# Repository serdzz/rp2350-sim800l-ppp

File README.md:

# RP2350-Plus + SIM800L → PPP → embassy-net

Embassy-приложение для Waveshare RP2350-Plus, которое поднимает интернет через
GSM-модуль SIM800L: настройка модема на `atat`, IP-канал на `embassy-net-ppp`,
сокеты на `embassy-net`.

```
┌──────────── командный режим ────────────┐   ┌──────── data-режим ────────┐
 BufferedUart ──► atat::Ingress ──► ResponseSlot / UrcChannel
      ▲                                          BufferedUart ──► embassy-net-ppp
      └── atat::Client ── AT+CGDCONT / ATD*99#                          │
                                                          embassy-net (TCP/UDP/DNS)
```

Один и тот же UART обслуживает обе фазы, но **никогда одновременно**. Пока идёт
AT-настройка, задача ingress живёт внутри `select` и снимается автоматически, как
только модем ответил `CONNECT`. После этого UART целиком уходит в
`embassy_net_ppp::Runner::run`. Когда PPP-сессия разваливается, приложение шлёт
`+++` / `ATH`, возвращается в командный режим и повторяет цикл.

## Документация

* [ARCHITECTURE.md](ARCHITECTURE.md) — как собрана прошивка: задачи, потоки
  данных, ключевые решения и расход ресурсов.
* [hardware/nri-g13-shifter/](hardware/nri-g13-shifter/) — схема переходника
  монетоприёмника на BSS138 (KiCad).
* [docs/cmux.md](docs/cmux.md) — мультиплексор 27.010: формат кадров, ловушки
  спецификации, раздача каналов и находки на живом железе.

## Файлы

| Файл | Что внутри |
|---|---|
| `src/main.rs` | Инициализация периферии, стек, главный цикл «AT → PPP → восстановление» |
| `src/config.rs` | **APN, логин/пароль, строка дозвона, таймауты** — правьте здесь |
| `src/modem.rs` | AT-команды, ответы и URC для `atat` |
| `src/sim800l.rs` | Питание модуля и последовательность инициализации до `CONNECT` |
| `src/cmux.rs` | Протокол 27.010: кадры, сессия, управляющий канал — см. [docs/cmux.md](docs/cmux.md) |
| `src/cmux_transport.rs` | Раздача каналов CMUX поверх одного UART |
| `src/mqtt.rs` | Телеметрия и приём SMS в MQTT, подписка на команды |
| `src/led.rs` | Режимы зелёного светодиода на GP25 |
| `src/display.rs` | Экран SSD1306 по I2C: часы, заряд, шкала сигнала, состояние связи |
| `src/fuel.rs` | Топливомер MAX17048 на той же шине I2C |
| `src/coin.rs` | Кредит, коды монет, разбор команд (без зависимостей, тесты на хосте) |
| `src/coin_io.rs` | Линии монетоприёмника NRI G-13: снятие кода монеты и блокировка |
| `src/clock.rs` | Время от сети и шкала сигнала (без зависимостей, тесты на хосте) |
| `src/health.rs` | Счётчики обрывов связи (без зависимостей, тесты на хосте) |
| `src/app.rs` | Демо-нагрузка поверх поднятого IP: DNS + HTTP GET |
| `src/battery.rs` | Замер VSYS/VBAT, определение источника питания |
| `src/lipo.rs` | Кривая заряда Li-Po (без зависимостей, тестируется на хосте) |
| `src/fmt.rs` | Фасад логирования: `info!`/`warn!`/`unwrap!` → defmt или log |
| `src/usb_logger.rs` | USB CDC-ACM логгер (только в сборке `log-usb`) |
| `src/io_compat.rs` | Мост `embedded-io-async` 0.7 ↔ 0.6 (см. «Версии крейтов») |
| `at-tests/` | Хостовые тесты формата AT-команд и дайджестера |

## Схема подключения

| SIM800L | RP2350-Plus | Примечание |
|---|---|---|
| `TXD` | `GP1` (UART0 RX) | |
| `RXD` | `GP0` (UART0 TX) | **нужен делитель 3.3 В → 2.8 В** |
| `PWRKEY` | `GP2` | опционально, если модуль не стартует сам |
| — | `GP16` / `GP17` | SDA / SCL: экран SSD1306 и топливомер MAX17048 (I2C0) |
| — | `GP3`…`GP8` | линии монетоприёмника, см. ниже |
| `GND` | `GND` | общая земля обязательна |
| `VCC` | **отдельный источник 3.4–4.4 В** | 2 А импульсами |

Два момента, на которых спотыкается большинство сборок:

1. **Питание.** SIM800L в момент передачи потребляет до 2 А. От пина `3V3` платы
   он не заработает — нужен отдельный источник (Li-Ion, LDO на 4 В) и
   конденсатор 1000 мкФ рядом с модулем. Симптом нехватки тока — URC
   `NORMAL POWER DOWN` в логе.
2. **Уровни.** Вход `RXD` модуля рассчитан на 2.8 В. Подавать на него 3.3 В
   напрямую — за пределами спецификации; поставьте делитель или преобразователь
   уровней. Выход `TXD` (2.8 В) RP2350 читает как логическую единицу без
   доработок.

Пины UART меняются в `src/main.rs` (`p.PIN_0` / `p.PIN_1`), но оставайтесь в
пределах одного `UART0` — иначе поправьте и `bind_interrupts!`.

## Топливомер MAX17048

SparkFun Qwiic Fuel Gauge вешается на ту же шину I2C, что и экран: `GP16` (SDA)
и `GP17` (SCL), адрес `0x36`. Аккумулятор подключается к самому топливомеру, а
не к плате — он меряет напряжение прямо на банке.

Заряд выводится на экран рядом с часами. Если топливомера нет, там стоит
прочерк: пустое место читалось бы как «показа заряда не предусмотрено».

### Зачем он, если есть замер VSYS

Затем, что `battery.rs` меряет не банку, а VSYS, и **при воткнутом USB о
батарее не говорит ничего** — VBUS через диод задаёт VSYS независимо от её
состояния. В логе это видно как «батарея не измеряется» в каждой строке.

У MAX17048 такого ограничения нет. И считает он заряд не по напряжению, а по
своей модели разряда: под нагрузкой напряжение проседает, и пересчёт
«вольты → проценты» врёт тем сильнее, чем больше ток. У модема этот ток
доходит до двух ампер.

### Про общую шину

Экран работает с шиной асинхронно, а крейт `max170xx` блокирующий. Свести их
удалось потому, что `embassy_rp::I2c` реализует оба трейта сразу: экран ходит
через асинхронную обёртку `I2cDevice`, а топливомер берёт мьютекс и обращается
к шине напрямую. Транзакция там короткая, пара байт, так что блокировка внутри
асинхронной задачи безобидна.

## Монетоприёмник NRI G-13

Вариант с шестью параллельными линиями (не последовательный интерфейс).

| Контакт разъёма | Сигнал | RP2350-Plus |
|---|---|---|
| 1 | `GND` | `GND` |
| 2 | `UB` +12 В | отдельный источник 10–16 В, ~20 мА |
| 7 | output line 1 | `GP3` |
| 8 | output line 2 | `GP4` |
| 9 | output line 3 | `GP5` |
| 10 | output line 4 | `GP6` |
| 3 | output line 5 | `GP7` |
| 4 | output line 6 | `GP8` |
| 6 | total blocking | `GP9` через ключ, см. ниже |

Нумерация контактов и линий не совпадает — сверяйтесь с таблицей, а не со
здравым смыслом.

Каждая линия **двунаправленная**: приёмник выдаёт по ней импульс 100 мс при
опознанной монете, и она же, удерживаемая в нуле, блокирует свой канал.
Поэтому в прошивке это `Flex`, а не обычный вход: открытый канал — вход с
подтяжкой, закрытый — выход, притянутый к земле. Высокий уровень на линию не
выдаётся никогда — с той стороны открытый коллектор.

### Согласование уровней: BSS138 на каждую линию

Линии приёмника живут в 12-вольтовом мире, плата — в 3,3-вольтовом, и по
каждой линии нужно и читать, и писать. Проверенное решение — **двунаправленный
преобразователь на BSS138**, по одному на линию:

```text
        +3.3 В (затвор)
             │
   GP3 ──────┤ BSS138 ├────── output line 1
   (вход с      (сток к приёмнику,
    подтяжкой)   исток к плате)
```

Внешние резисторы не нужны: со стороны платы работает встроенная подтяжка
RP2350 (её включает `Flex::set_pull(Pull::Up)`), со стороны приёмника — его
собственная. Так собран рабочий автомат на MSP430
(`bahilizator_svn/hardware/main_baord/coin.sch`, `Q10…Q15`), и там же прошивка
включает внутренние подтяжки контроллера.

Для справки, требования из схемы подключения (`G-13.6000-1 d`, стр. 22):

| | напряжение |
|---|---|
| блокировка канала | `≤ 1 В` |
| приём канала | `≥ 3,5 В` |
| допустимое на линии | до 35 В, до 150 мА |

Заводить линии на выводы напрямую **нельзя**: 3,3 В ниже порога приёма, и это
ещё до вопроса о том, что на линии может оказаться.

### Полная блокировка (контакт 6)

Закрывает приём целиком, независимо от поканальной маски. Активен **высоким**:
блокировка `≥ 3,5 В`, приём `≤ 1 В`, выдерживает до 35 В.

Схема та же, что у линий, плюс подтяжка стока к `+5 В` — так это сделано в
рабочем автомате (`Q5` и `R45` 10 кОм на той же схеме):

```text
                        +3.3 В        +5 В
                           │            │
                           │           10к
                           │            │
  GP9 ──10к── +3.3 В   ────┤ BSS138 ├───┴──── контакт 6 (total blocking)
```

Каскад **не инвертирует**: `GP9` высокий → полевик закрыт → 10к тянет линию к
5 В → блокировка. Поэтому в `src/config.rs`:

```rust
pub const COIN_TOTAL_BLOCK_INVERTED: bool = false;
```

Резистор 10 кОм от `GP9` к `+3.3 В` — не из схемы-образца, а добавка: без него
вывод в сбросе не управляется, линия уходит к нулю, и **мёртвый автомат
принимает монеты, не давая кредита**. С подтяжкой неуправляемый вывод означает
«заблокировано».

Если собрали инвертирующий каскад (например, NPN с подтяжкой к +12 В),
поставьте `COIN_TOTAL_BLOCK_INVERTED = true`.

### Монета опознаётся кодом на линиях

Прошивка снимает состояние всех шести линий разом и ищет получившийся код в
таблице. Это покрывает оба способа, которыми приёмник умеет сообщать монету:

* **одна монета на линию** — код однобитный (`0b010000` = линия 5);
* **двоичный код** — код многобитный (`0b000101` = пины 1 и 3 вместе).

Второе документация допускает прямо: «possible to transmit coin signals in a
binary code or assign more than one line to a type of coin».

Считать линии по отдельности нельзя: при двоичном коде одно евро зажигает два
пина, и шесть независимых счётчиков насчитали бы две монеты.

### Столбец на шильдике читается двояко — решает монета

Значения 1…6 в столбце — это либо номер линии, либо код. Глазами это не
различить, поэтому в `src/config.rs` перечислены **оба** варианта:

```rust
pub const COINS: &[coin::Coin] = &[
    coin::Coin { mask: 0b010000, value: 100, name: "EUR 1 (линия 5)" },
    coin::Coin { mask: 0b000101, value: 100, name: "EUR 1 (код 5)" },
    coin::Coin { mask: 0b100000, value: 100, name: "жетон (линия 6)" },
    coin::Coin { mask: 0b000110, value: 100, name: "жетон (код 6)" },
];
```

Столкнуться они не могут: при однобитной раскладке `0b000101` не появится
никогда (две линии разом не зажигаются), при двоичной не появится `0b010000`
(кода 16 на шильдике нет). Бросьте монету — лог скажет, какой вариант ваш:

```
COIN: EUR 1 (линия 5) (код 0b010000), номинал 100, кредит 100
```

Увидели — лишнюю строку из таблицы удалите. Неизвестный код печатается готовым
к вписыванию.

Для справки, что на шильдике экземпляра `06V01/5-14000084-008` (11/06):

| Столбец | Монета | Каналы |
|---|---|---|
| 1 | LVL 1,- | 01, 06 |
| 2 | RUR 5,- | 02, 07 |
| 3 | UAH 0,50 | 03, 08 |
| 4 | UAH 1,- | 04, 09 |
| 5 | **EUR 1,-** | 05, 10 |
| 6 | жетон | 12…16 |

Жетоны различить нельзя — все пять каналов дают один код.

### Ненужные монеты глушите переключателями, а не линиями

Латы, рубли и гривны прошивка не засчитает, но приёмник их всё равно
**проглотит** — они провалятся в кассу, а клиент останется без товара и без
денег. Закрывать их надо на самом приёмнике, по каналам:

* `S1.1…8` — каналы 1–8, `S2.1…8` — каналы 9–16;
* монета занимает **два канала** (обычная полоса приёма и узкая), выключать
  надо оба: лат — это `S1.1` и `S1.6`.

Команда `coin/block` глушит линии и остаётся полезной при однобитной раскладке.
При двоичном коде она почти бесполезна: пин 1 участвует и в лате, и в гривне, и
в евро, так что закрытие линии калечит чужие коды. Поэтому
`COIN_BLOCK_DEFAULT` равен нулю.

### Можно ли принимать евро кроме одного

Только 1 € запрограммирован заводом. Два блока настроек (`B-0` / `B-1`,
переключатель `S1.10`) у этого экземпляра содержат одинаковые наборы, так что
переключение ничего не даст.

Зато доступно обучение: `S2.9` = TEACH Mode, учить можно каналы 10 и 11, из
которых **11 свободен**. Порядок: `S2.9` в TEACH, `S2.3` (канал 11) включить,
бросить монету 10 раз до щелчка заслонки, оба переключателя выключить — второй
щелчок означает, что записалось. Два щелчка вместо одного — не записалось,
обычно из-за перекрытия с уже известной монетой; тогда повторить с `S2.10` в
положении `Teachband wide`.

Полный набор евро (10/20/50 центов, 2 €) требует программатора NRI с
программой KUNEMP.

### Переключатели на корпусе

| Группа | Позиции | Функция |
|---|---|---|
| S1 | 1…8 | заглушить каналы 1–8 |
| S1 | 9 | CASINO / NORMAL |
| S1 | 10 | Block 1 / Block 0 |
| S2 | 1…8 | заглушить каналы 9–16 |
| S2 | 9 | TEACH / NORMAL |
| S2 | 10 | Teachband wide / normal |

## Топики MQTT

| Топик | Направление | Тело |
|---|---|---|
| `rp2350-sim800l/csq` | публикуем, retain | `<rssi>` из `+CSQ`, раз в 60 с |
| `rp2350-sim800l/sms` | публикуем, retain | текст принятого SMS |
| `rp2350-sim800l/coin` | публикуем | `{"coin":"EUR 1","code":5,"value":100,"credit":100}` |
| `rp2350-sim800l/led` | подписаны | `ON`, `OFF`, `BLINK`, `TOGGLE` |
| `rp2350-sim800l/coin/block` | подписаны | `none`, `all`, `1,3` — какие линии заблокировать |
| `rp2350-sim800l/sms/send/<номер>` | подписаны | текст SMS в теле, номер в топике |
| `rp2350-sim800l/coin/total` | подписаны | `block` / `accept` — закрыть приём целиком |

Событие монеты идёт без `retain`: оно имеет смысл в момент наступления, а не
как последнее известное состояние. Команда блокировки, наоборот, задаёт
состояние целиком — присланная маска заменяет предыдущую, а не дополняет её.

Поканальная и полная блокировки независимы: закрытый автомат не отменяет того,
какие монеты в нём не принимаются, когда он открыт. Тело `block`/`accept`, а не
`on`/`off`, потому что «ON» одинаково правдоподобно читается и как «блокировка
включена», и как «приём включён». Пока приём закрыт, на экране рядом с кредитом
горит `ЗАКРЫТО` — иначе закрытый приёмник выглядит как сломанный.

### Отправка SMS

Номер — последний сегмент топика, текст — тело сообщения:

```bash
mosquitto_pub -h broker.hivemq.com \
  -t rp2350-sim800l/sms/send/37120000000 -m 'Coin jam on line 3'
```

**Номер только цифрами, без плюса.** В имени топика MQTT плюс запрещён — это
подстановочный знак, — и брокер такую публикацию отвергнет. Прошивка
подставляет его сама.

**Текст только ASCII, до 160 символов.** Кириллица требует `AT+CSCS="UCS2"` и
перекодировки всего сообщения вместе с номером; отправить её как есть — значит
получить абракадабру, поэтому прошивка честно отказывается и пишет причину в
лог.

Отправка идёт не из MQTT-задачи, а из той, что держит AT-канал: она занимает
секунды и требует модема, а MQTT-клиент за это время потерял бы соединение по
keepalive. Между командой и отправкой сообщение лежит в очереди на четыре
штуки.

```bash
# закрыть приём целиком
mosquitto_pub -h broker.hivemq.com -t rp2350-sim800l/coin/total -m 'block'

# заблокировать первую и третью линии
mosquitto_pub -h broker.hivemq.com -t rp2350-sim800l/coin/block -m '1,3'
# снять блокировку
mosquitto_pub -h broker.hivemq.com -t rp2350-sim800l/coin/block -m 'none'
```

## Настройка под оператора

Всё в `src/config.rs`:

```rust
pub const APN: &str = "internet";          // APN оператора
pub const PPP_USERNAME: &[u8] = b"";       // PAP-логин, обычно пустой
pub const PPP_PASSWORD: &[u8] = b"";
pub const DIAL_STRING: &str = "*99***1#";  // некоторые прошивки хотят "*99#"
```

## Логи: два бэкенда

Выбираются feature-флагом, включён должен быть ровно один. Макросы
`info!`/`warn!`/`error!`/`debug!`/`unwrap!` объявлены в `src/fmt.rs` и
разворачиваются либо в `defmt`, либо в `log` — код приложения от выбора не
зависит.

| | `log-rtt` (по умолчанию) | `log-usb` |
|---|---|---|
| Транспорт | RTT через отладчик | USB CDC-ACM (виртуальный COM-порт) |
| Нужен отладчик | да | **нет** |
| Чем читать | `probe-rs` / `cargo run` | любой serial-терминал |
| Паники | печатаются с бэктрейсом | не видны (см. ниже) |
| Flash | ~197 КиБ | ~201 КиБ |
| RAM (bss) | ~44 КиБ | ~45 КиБ |

### `log-usb`: лог по USB, без отладчика

```bash
cargo build-usb        # алиас в .cargo/config.toml

# BOOTSEL + USB, затем:
picotool load -u -v -x -t elf target/thumbv8m.main-none-eabihf/release/rp2350-sim800l

# Плата поднимется как виртуальный COM-порт:
screen /dev/tty.usbmodem*  115200      # macOS
picocom /dev/ttyACM0 -b 115200         # Linux
```

Скорость порта роли не играет — CDC-ACM её игнорирует. Формат строки:

```
[INFO ] 4.312 SIM800L: CPIN = READY
```

Если читаете порт скриптом, а не `screen`/`picocom`, переведите tty в raw —
иначе терминальная дисциплина портит многобайтные UTF-8 символы (кириллица
в логе поедет):

```bash
stty -f /dev/cu.usbmodem* raw -echo -istrip
```

Готовый вариант со всем этим внутри:

```bash
./tools/capture-log.py 120        # 120 секунд лога
```

Он же говорит, если порт занят: терминал держит устройство монопольно, и
запущенный `screen` со стороны выглядит как намертво замолчавшая плата.

Что стоит знать про этот режим:

* **Первые строки теряются.** Хост enumerate'ит порт около секунды; всё, что
  приложение успело написать раньше, оседает в буфере на 2 КиБ и вытесняется.
  Чтобы поймать самый старт — держите терминал открытым и передёрните плату
  кнопкой RUN.
* **Паники не видны.** `panic-probe` без `print-defmt` просто выполняет `udf`,
  а отправить сообщение через USB уже некому: executor остановлен. Отлаживать
  паники нужно в RTT-сборке.
* **`atat` молчит.** У версии 0.24 нет feature `log`, поэтому её внутренние
  сообщения в этом режиме пропадают. Логи самого приложения не страдают.
* VID/PID `0xc0de:0xcafe` — тестовая пара из примеров Embassy. Для серийного
  изделия нужна своя.

Порог логирования и размер буфера — константы `LEVEL` и `LOG_BUF_SIZE` в
`src/usb_logger.rs`.

### Диагностика подключения к сети

Лог при инициализации показывает не «получилось / не получилось», а причину:

```
SIM800L: IMSI 2470xxxxxxxxxxx — домашняя сеть MCC 247 / MNC 02
SIM800L: CSQ 20 (-73 дБм) | CREG 2 — ищет сеть | CGREG 2 — ищет сеть
SIM800L: регистрации нет; сканирую сети (AT+COPS=?, до 3 мин)…
SIM800L: видимые сети: +COPS: (2,"TELE2","TELE2","24702"),(1,"LMT GSM",...)
```

Как читать `<stat>` из `+CREG?` / `+CGREG?`:

| `stat` | Значение | Куда копать |
|---|---|---|
| 0 | не ищет | радиотракт выключен |
| 1 / 5 | зарегистрирован (дома / роуминг) | норма |
| 2 | ищет сеть | питание, антенна или сети нет в эфире |
| 3 | **отказано** | сеть видна, но не пускает: SIM, тариф или роуминг |

`AT+COPS=?` (за флагом `SCAN_OPERATORS_ON_FAILURE`) показывает все сети в
эфире; первое число в скобках — `2` текущая, `1` доступна, `3` запрещена.
`IMSI` даёт домашнюю сеть карты — сравнив её со списком, видно, отказывает
свой оператор или чужой в роуминге.

**Перезагрузки модуля отслеживаются отдельно.** `RDY` во время ожидания
регистрации прерывает цикл сразу, а не через две минуты опроса уже
перезагрузившейся железки. Три перезагрузки подряд — почти наверняка провал
питания: регистрация идёт на полной мощности передатчика, и просадка сбрасывает
модуль ровно в этот момент.

## Сборка и прошивка

```bash
rustup target add thumbv8m.main-none-eabihf

# С отладчиком (Picoprobe / Raspberry Pi Debug Probe) — сразу видно defmt-лог:
cargo run --release

# Без отладчика: зажать BOOTSEL, воткнуть USB, затем
cargo build --release
picotool load -u -v -x -t elf target/thumbv8m.main-none-eabihf/release/rp2350-sim800l
```

`probe-rs` для RP2350 указан в `.cargo/config.toml` как `--chip RP235x`.

`memory.x` задан под 4 МиБ flash (минимальная комплектация RP2350-Plus). Для
16-мегабайтной версии поднимите `LENGTH` у `FLASH` до `16384K`.

Размеры выше — для сборки со включённым `USE_CMUX` и MQTT. Обе ветки подъёма
компилируются в один образ, поэтому флаг стоит около 18 КиБ; подробности в
[ARCHITECTURE.md](ARCHITECTURE.md).

## Питание: батарея, VBAT и SIM800L

Разобрано по [официальной схеме RP2350-Plus](https://files.waveshare.com/wiki/RP2350-Plus/RP2350_Plus.pdf).

```text
  VBUS ──┤>├─ D1 ──┬── VSYS ──┬── R1 200K ─┬─ Q1 SI2306 ── GP29/ADC3
  VBAT ──┤>├─ D2 ──┘          │            ├─ R7 100K ── GND
   ▲  (P3, PH1.25)            │            └─ C7 100nF ── GND
   └── ETA6096 (заряд 1 А)    └── MP28164 (buck-boost) ── 3V3
```

### Измерение напряжения

Реализовано в `src/battery.rs`, задача логирует раз в минуту.

| Сигнал | Что это |
|---|---|
| `GP29` / `ADC3` | **VSYS / 3** — делитель R1 200K / R7 100K, как на Pico |
| `GP24` | сенсор VBUS: высокий = воткнут USB |
| `GP23` | `MODE/SYNC` у MP28164: высокий = постоянная ШИМ |

`Q1` (SI2306) стоит между делителем и GP29, затвор жёстко на 3V3. Управлять им
не нужно — пока плата запитана, он открыт; когда 3V3 снят, он отвязывает GP29
от VSYS, чтобы делитель не питал ногу МК и не сажал аккумулятор.

На время замера код поднимает `GP23`: в энергосберегающем режиме преобразователя
пульсации VSYS дают разброс в десятки милливольт.

Два ограничения, которые надо принять как данность:

* **При воткнутом USB напряжение батареи не измеряется.** VSYS задаёт VBUS через
  D1 (≈4.7 В) независимо от аккумулятора, а отдельной линии замера VBAT на плате
  нет.
* На батарее `VBAT = VSYS + Vf(D2)`. Падение на диоде зависит от тока, поэтому
  `SCHOTTKY_DROP_MV` в `src/battery.rs` — прикидка (250 мВ), которую стоит
  откалибровать вольтметром прямо на аккумуляторе.

### Куда подключать питание SIM800L

| Источник | Годится | Почему |
|---|---|---|
| `3V3` (пин 36) | **нет** | 3.3 В ниже минимума 3.4 В, а MP28164 не отдаст 2 А |
| `VSYS` (пин 39) | **нет** | при USB там ≈4.7 В — выше предела 4.4 В; на батарее импульсы 2 А идут через D2 и роняют VSYS так, что плата уходит в сброс |
| **VBAT** (разъём P3 или клеммы аккумулятора) | **да** | 3.4–4.2 В ровно в окне модуля, а импульсный ток берётся с самой банки |

VBAT на 40-пиновую гребёнку **не выведен** — доступ только через батарейный
разъём PH1.25-2P. Подключаться нужно параллельно ему: Y-переходник на PH1.25
либо пайка к клеммам аккумулятора.

```text
   [Li-Po] ──┬── PH1.25 ──► RP2350-Plus (P3)
             │
             └──────────────► SIM800L VCC
                              + 1000 мкФ low-ESR у самого модуля
   GND ── общая точка (звезда от минуса аккумулятора)
```

Что учесть:

* **Электролит 1000 мкФ low-ESR прямо на пины `VCC`/`GND` модуля — обязателен.**
  Не на рейку макетки, а на сам разъём. Проверено на этом стенде: без него
  модуль уходил в перезагрузку каждые ~11 секунд (14 сбросов за 172 с), с ним —
  ни одного за 140 с. Показательно, что умирал он ровно на первой передаче:
  `CSQ` успевал вырасти с 0 до 20, и через 6 мс приходил `Break error`.
  Приём модулю даётся на десятках миллиампер, а регистрация требует передачи
  на полной мощности — поэтому симптом выглядит как «сигнал есть, регистрации
  нет».
* **Провода к модулю — короткие и толстые.** Импульсы 2 А по 577 мкс с частотой
  216 Гц: лишние 100 мОм в проводе дают просадку 0.2 В.
* **Батарея должна отдавать 2 А.** Мелкая банка на 300–500 мА·ч просядет ниже
  3.4 В на первой же передаче, и модуль выдаст `NORMAL POWER DOWN`.
* **Заряд ограничен 1 А** (R13 = 160 кОм; 82 кОм → 2 А, 66 кОм → 2.5 А). Если
  SIM800L потребляет больше, чем даёт зарядник, аккумулятор разряжается даже при
  воткнутом USB.
* **Модуль будет запитан всегда**, пока подключена батарея — даже когда плата
  выключена через `3V3_EN`. Если это важно, ставьте ключ верхнего плеча
  (P-канальный MOSFET) на линию VCC модуля или уводите модуль в power-down
  через `PWRKEY`.
* Уровни UART не меняются: `TXD` модуля 2.8 В плата читает как единицу, а на
  `GP0 → RXD` по-прежнему нужен делитель.

## Сторожевой таймер

Устройство работает без присмотра, поэтому в прошивке включён watchdog RP2350:
порог 8 секунд, кормление раз в 2 секунды из отдельной задачи.

Кормление не безусловное. Задача, кормящая по таймеру, доказывает только то,
что исполнитель крутится, — а зависнуть можно и с живым исполнителем:

| Что сломалось | Что замечает |
|---|---|
| паника, холостой цикл, зависший исполнитель | кормить некому |
| обмен с модемом встал при живых задачах | 10 минут молчания модема |

Порог молчания щедрый намеренно: в рабочем режиме модем отвечает не реже чем
раз в 30 секунд (опрос CSQ), но `AT+COPS=?` сканирует сети молча и занимает
минуты. Перезагрузка посреди сканирования была бы хуже болезни.

### PWRKEY и тёплый перезапуск

Импульс PWRKEY **переключает** питание SIM800L, а не включает его. После
перезагрузки по сторожевому таймеру модуль остался работать, и импульс бы его
выключил — поэтому на тёплом перезапуске он пропускается.

Тёплый перезапуск отличается от холодного старта по скретч-регистру watchdog:
он переживает перезагрузку чипа, но обнуляется при потере питания.

Если предположение окажется неверным и модуль всё-таки выключен, три неудачных
подъёма подряд (около полуминуты) заставят прошивку дёрнуть PWRKEY.

В логе перезагрузка видна строкой `WDT: прошлый запуск оборвала перезагрузка`.

## Тесты

```bash
./run-at-tests.sh
```

Гоняет на хосте ровно тот `src/modem.rs`, что уходит в прошивку, и проверяет
байты на проводе, разбор ответов и поведение дайджестера. Два случая, которые
эти тесты закрывают, и на которых легко обжечься:

* `ATD*99***1#` должна уйти **без кавычек** — по умолчанию `atat` заключает
  строковые аргументы в кавычки, и модем на `ATD"*99***1#"` отвечает `ERROR`.
  Отсюда `quote_escape_strings = false` у `DialPpp`.
* В перечислении `Urc` не должно быть префиксов, которые приходят ответом на
  наши же команды (`+CREG`, `+CSQ`, `+CPIN`, `+CGATT`). Дайджестер `atat`
  проверяет URC-теги **до** разбора ответа, так что такой тег увёл бы ответ в
  URC-канал, а `send()` завис бы до таймаута.

## Версии крейтов

В графе зависимостей намеренно уживаются по две версии трёх крейтов — это
следствие того, что `atat` 0.24 отстаёт от текущего Embassy:

| Крейт | `atat` | Embassy | Как разрешено |
|---|---|---|---|
| `embedded-io-async` | 0.6 | 0.7 | обёртка `Compat` в `src/io_compat.rs` |
| `heapless` | 0.8 | 0.9 | типы AT-команд используют `atat::heapless` |
| `embassy-time` | 0.4 | 0.5 | обе версии ходят в один `embassy-time-driver` 0.2, драйвер даёт `embassy-rp` — работает корректно |

Когда `atat` обновится, `src/io_compat.rs` удаляется, а `Compat(x)` в
`src/main.rs` заменяется на `x`.

## Что дальше

Полезная логика пишется в `src/app.rs` — `Stack<'static>` даёт обычные
TCP/UDP/DNS сокеты `embassy-net`. Для HTTP удобно добавить `reqwless`, для
MQTT — `rust-mqtt`; оба работают поверх `embassy-net` без изменений в этом коде.

Что стоит доделать под конкретную задачу:

* **Аппаратный flow control.** Без RTS/CTS единственная защита от переполнения —
  2 КиБ RX-буфера UART. Если модуль разведён с `RTS`/`CTS`, переключитесь на
  `BufferedUart::new_with_rtscts` и добавьте `AT+IFC=2,2` в `bring_up`.
* **Watchdog.** `embassy_rp::watchdog` на случай, если модем зависнет в
  состоянии, из которого `+++`/`ATH` не вытаскивает.
* **Экономия энергии.** `AT+CFUN=0` между сеансами и `AT+CSCLK=2` для сна модуля.

## Лицензия

Двойная, на выбор: [MIT](LICENSE-MIT) или [Apache-2.0](LICENSE-APACHE) — как
принято в экосистеме Rust и в самом Embassy.

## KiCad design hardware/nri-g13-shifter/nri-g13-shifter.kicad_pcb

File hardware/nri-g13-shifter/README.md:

# Переходник NRI G-13 ↔ RP2350-Plus

Плата согласования уровней между монетоприёмником NRI G-13 (12 В) и платой
RP2350-Plus (3.3 В). Шесть линий монет и линия полной блокировки.

Открывать: `nri-g13-shifter.kicad_pro`. Для просмотра без KiCad —
[nri-g13-shifter.pdf](nri-g13-shifter.pdf).

## Зачем она нужна

Линии приёмника **двунаправленные**: по одной и той же линии приходит импульс
об опознанной монете и задаётся блокировка канала — удержанием линии в нуле.
Напрямую с выводом RP2350 их соединять нельзя:

| | из даташита `G-13.6000-1 d`, стр. 22 |
|---|---|
| блокировка канала | `≤ 1 В` |
| приём канала | `≥ 3,5 В` |
| допустимо на линии | до 35 В, до 150 мА |

Порог приёма **3,5 В выше, чем выдаёт плата**. Отсюда двунаправленный
преобразователь на BSS138 — по одному на линию: затвор на 3.3 В, исток к
плате, сток к приёмнику. Ровно так сделано в предыдущем поколении устройства
(`bahilizator_svn/hardware/main_baord/coin.sch`, `Q10…Q15`).

## Разъёмы

**J1** — к приёмнику, 10 контактов. Нумерация контактов и линий **не
совпадает**, это не опечатка:

| Контакт | Сигнал | Цепь |
|---|---|---|
| 1 | GND | `GND` |
| 2 | UB +12 В | `+12V` |
| 3 | output line 5 | `LINE5` |
| 4 | output line 6 | `LINE6` |
| 5 | return | не подключён |
| 6 | total blocking | `INHIBIT` |
| 7 | output line 1 | `LINE1` |
| 8 | output line 2 | `LINE2` |
| 9 | output line 3 | `LINE3` |
| 10 | output line 4 | `LINE4` |

Контакт 5 не подключаем: он нужен только варианту Casino, где по нему идёт
сигнал датчика приёма.

**J2** — единственный разъём к остальному устройству, 12 контактов. Питание
приёмника идёт через него же: отдельный клеммник означал бы второй кабель к
устройству, которое и так стоит в тесном корпусе.

| Контакт | Цепь | Куда |
|---|---|---|
| 1 | `+12V` | внешний источник 10–16 В, ~20 мА |
| 2 | `GND` | общая земля |
| 3 | `+3V3` | с платы RP2350-Plus |
| 4 | `GND` | |
| 5…11 | `GP3`…`GP9` | линии 1…6 и блокировка |
| 12 | `GND` | |

12 В на плату RP2350-Plus, разумеется, не подаётся — этот контакт идёт мимо
неё, прямо к источнику.

## Что и зачем стоит

| Позиции | Что | Зачем |
|---|---|---|
| Q1…Q7 | BSS138 | двунаправленное согласование 3.3 В ↔ 12 В |
| R1…R7 | 10 кОм к 3.3 В | подтяжка со стороны платы |
| R17 | 10 кОм к 12 В | **обязателен**: без него на входе блокировки не наберётся 3,5 В |
| R11…R16 | 10 кОм к 12 В | по месту, см. ниже |
| D1…D6 + R21…R26 | светодиод и 1 кОм | индикация импульса монеты |
| C1…C3 | 100n, 100n, 10µ | развязка по питанию |

### R11…R16 ставить не спешите

Линии монет — открытый коллектор, и подтягивать их должен кто-то один.
Приёмник обычно делает это сам. Измерьте линию относительно земли на
запитанном приёмнике, ничего к ней не подключая:

* **есть напряжение** — приёмник тянет сам, эти резисторы не нужны;
* **ноль или болтается** — поставьте.

Поэтому в схеме они помечены как неустанавливаемые (в KiCad — крестом).

### R7 держит автомат закрытым, пока контроллер в сбросе

`R7` подтягивает `GP9` к 3.3 В. Каскад не инвертирует: высокий уровень на
`GP9` → полевик закрыт → `R17` тянет линию к 12 В → **блокировка**.

Пока контроллер в сбросе, вывод не управляется, и без этого резистора линия
ушла бы к нулю — мёртвый автомат принимал бы монеты, не давая кредита. С ним
неуправляемое состояние совпадает с безопасным.

В прошивке этому соответствует `COIN_TOTAL_BLOCK_INVERTED = false`.

### Светодиода на GP9 нет намеренно

Он с резистором перетянул бы подтяжку `R7` и сломал бы ровно то свойство, ради
которого она стоит.

## Индикаторы отвечают на открытый вопрос

Светодиод горит, пока линия притянута к нулю, то есть весь импульс монеты
(100 мс). Этого хватает, чтобы **без прошивки** понять, как приёмник сообщает
о монете:

* мигнул **один** светодиод — одна монета на линию;
* мигнули **два** — двоичный код.

Это тот самый вопрос, который сейчас не решён: в `config::COINS` лежат оба
варианта, и первая же брошенная монета покажет, какой из них ваш.

## Плата

| верх | низ |
|---|---|
|  |  |

Два слоя, **78 × 79 мм**, земля залита с обеих сторон.

| | ширина |
|---|---|
| магистральные шины 3.3 В и 12 В | 1.2 мм |
| отводы питания | 0.8 мм |
| сигналы | 0.3 мм |

Ток тут копеечный — приёмник берёт около 20 мА, — так что ширина питания взята
не по нагреву, а ради надёжности: такую дорожку труднее подорвать при монтаже и
переделках.

Строка канала сжата до 8 мм за счёт того, что полосы внутри неё не
перекрываются по горизонтали: индикатор и отвод к разъёму делят одну высоту,
просто живут на разных участках платы.

Разводка ортогональная, и это не украшательство, а то, что позволило её
сгенерировать:

* **верх** — сигналы, горизонтальными строками, по строке на канал;
* **низ** — питание, вертикальными шинами, пересекающими все строки.

Пересечься они не могут по построению, а семь строк отличаются только
координатой `y`.

Две тонкости, которые пришлось развести руками:

* **Отвод к разъёму обходит R11…R17 сверху.** В линию его не поставить — там
  уже сидит сток полевика, и дорожка к разъёму упёрлась бы в резистор.
* **Разбор разъёма приёмника идёт по двум слоям.** Порядок контактов там свой
  и в строки ложится с перехлёстом; половина линий уходит вниз, и внутри
  каждой половины порядок уже монотонный, то есть пересечений нет.

Разбор гребёнки платы, наоборот, однослойный: её выводы и строки идут в одном
порядке, и веер получается непересекающимся сам собой.

### Про заливку

Земля залита по обоим слоям, и обе заливки получились сплошными: сигналы
живут наверху горизонтальными полосами, питание внизу вертикальными, и ни то,
ни другое не режет плату поперёк.

Дорожки земли под заливкой оставлены намеренно. Заливка на плотной плате может
разорваться на куски, и надеяться, что все они окажутся связаны, нельзя, —
а дорожка связывает гарантированно.

Сшивающие отверстия стоят **строго на этих дорожках**, а не в чистом поле:
отверстие, висящее в заливке, связью не считается ни для проверки, ни на
плате, если медь вокруг него окажется отрезанной. Это, кстати, единственная
ошибка, которую KiCad поймал в заливке: тринадцать отверстий по нижнему краю
оказались висящими, и их пришлось переставить.

## На производство

```bash
./make_gerbers.sh
```

Кладёт в `gerber/` полный комплект и собирает `nri-g13-shifter-gerber.zip` —
его и загружать на завод.

| Параметр | Значение |
|---|---|
| Слоёв | 2 |
| Размер | 78 × 79 мм |
| Толщина | 1.6 мм |
| Минимальная дорожка | 0.3 мм |
| Минимальный зазор | 0.2 мм |
| Отверстия | 0.6 мм (переходные, 50 шт) и 1.0 мм (разъёмы, 22 шт) |
| Поясок переходного | 0.2 мм |

Ничего дефицитного тут нет: дешёвые заводы держат 0.127 мм по дорожке и
0.2 мм по отверстию, то есть запас двукратный и больше.

Отчёт по сверловке — заодно проверка замысла: 50 отверстий по 0.6 мм это ровно
переходные, 22 по 1.0 мм — контакты двух разъёмов. Несовпадение здесь означало
бы, что на плате есть что-то, чего в разводке не задумывалось.

**`--check-zones` в скрипте обязателен.** Заливку заполняет KiCad, а не
`gen_pcb.py`, и без этого флага на завод уехала бы плата с пустыми зонами —
то есть без земли.

## Монтаж на заводе

`make_gerbers.sh` кладёт в `assembly/` то, без чего на монтаж не примут:

| Файл | Что это |
|---|---|
| `bom.csv` | перечень элементов с артикулами склада |
| `cpl.csv` | координаты и поворот каждого элемента |

`--exclude-dnp` стоит в обоих вызовах: `R11…R16` ставить не нужно, и завод не
должен узнавать об этом из примечания в письме.

### Порядок заказа на JLCPCB

1. **Плата.** На главной «Order now», загрузить `nri-g13-shifter-gerber.zip`.
   Размер и число слоёв подхватятся сами: 78 × 79 мм, два слоя. Из настроек
   менять нечего — толщина 1.6 мм и покрытие HASL идут по умолчанию.
   Минимальный тираж плат — 5 штук.

2. **Включить монтаж.** Переключатель `PCB Assembly`. Сторона — только
   верхняя, все элементы там. Количество собираемых плат можно взять меньше,
   чем плат: собрать две, а три оставить про запас, выйдет заметно дешевле.

3. **Загрузить файлы.** `assembly/bom.csv` в поле BOM, `assembly/cpl.csv` в
   поле CPL. Разъёмы в них исключены намеренно — см. ниже.

   Оба файла уже приведены к тому виду, который завод принимает: обозначения
   перечислены поштучно, а не диапазонами вида `D1-D6`, и шапка координат
   названа так, как ждёт JLCPCB — `Designator, Mid X, Mid Y, Rotation, Layer`.
   KiCad по умолчанию делает и то, и другое по-своему, а завод на этом
   спотыкается молча: `File processing failed` без единой подробности.

4. **Сверить детали.** Шесть строк должны опознаться по артикулам без ручного
   подбора. Проверить наличие на складе: артикулы верные, но остатки живут
   своей жизнью.

5. **Сверить установку — не пропускать этот шаг.** Показывают плату с
   расставленными деталями. Смотреть надо на светодиоды и BSS138: соглашение о
   нуле поворота у KiCad и у завода совпадает не всегда. Для светодиода
   ошибка означает обратную полярность, то есть шесть неработающих
   индикаторов.

6. Корзина, доставка, оплата.

Разъёмы `J1` и `J2` придётся припаять самому: выводной монтаж у JLCPCB —
отдельная услуга, а двадцать два вывода паяются руками за десять минут.
Купить их проще локально, чем ждать в той же посылке.

Из чего складывается цена: сами платы, разовая настройка станка, разовая плата
за расширенную позицию (`BSS138`), стоимость деталей и доставка. Точные суммы
показывает корзина — на глаз это десятки долларов, а не сотни, но верить надо
корзине, а не мне.

### Артикулы JLCPCB

Проставлены в схеме, при компонентах, и оттуда попадают и в `bom.csv`, и в
плату. Все сверены по каталогу, а не восстановлены по памяти: неверный код —
это не опечатка, а другая деталь на плате.

| Позиция | Артикул | Что это | Набор |
|---|---|---|---|
| R1…R7, R17 | `C25804` | 10 кОм 0603 1% | базовый |
| R21…R26 | `C23179` | 470 Ом 0603 1% | базовый |
| C1, C2 | `C14663` | 100 нФ 50 В 0603 X7R | базовый |
| C3 | `C15849` | 1 мкФ 50 В 0603 | базовый |
| D1…D6 | `C2286` | светодиод красный 0603 | базовый |
| Q1…Q7 | `C78284` | BSS138 SOT-23, порог 0.8 В | расширенный |

За расширенную позицию берут разовую плату за настройку станка. Менять BSS138
на базовый 2N7002 (`C8545`) не стоит: у того порог отпирания вдвое выше, а весь
смысл каскада в том, чтобы он открывался от 3.3 В.

**Светодиод именно красный.** Зелёный в корпусе 0603 имеет прямое напряжение
3.3 В — ровно столько, сколько на шине, — и от неё попросту не зажёгся бы.
У красного 1.8…2.4 В, и через 470 Ом получается около 3 мА: для вспышки длиной
100 мс этого хватает уверенно.

Артикулы стоит перепроверить на наличие в момент заказа — склад живёт своей
жизнью.

### Два номинала исправлены при подборе артикулов

Оба раза ошибка была не в схеме, а в том, чего в схеме не написано.

**`C3`: было 10 мкФ, стало 1 мкФ.** В корпусе 0603 десять микрофарад бывают
только на 10 вольт, а `C3` сидит на шине 12 В — номинал был просто
неработоспособен. В схеме написано «10u», рабочего напряжения там нет, а в
каталоге есть.

**`R21…R26`: было 1 кОм, стало 470 Ом.** Заодно сменился цвет светодиода, и по
той же причине: у зелёного прямое напряжение равно напряжению шины.

### Две вещи, которые придётся сделать руками

**Повороты.** Соглашение о нуле поворота у KiCad и у заводов совпадает не
всегда — чаще всего расходятся как раз светодиоды и SOT-23. В просмотрщике
заказа видно, куда смотрит первый вывод; сверьтесь по нему, прежде чем платить.
Для светодиода это ещё и полярность.

**Разъёмы.** `J1` и `J2` — выводной монтаж, у большинства заводов это отдельная
услуга, дороже поверхностного. Двадцать два вывода паяются руками за десять
минут, так что дешевле исключить их из заказа и поставить самому.

## Как пересобрать

Схема генерируется скриптом: семь каналов отличаются только именами цепей, и
копировать их мышью — верный способ ошибиться в одном из семи.

```bash
python3 gen_sch.py                                    # схема + bom.md
kicad-cli sch erc nri-g13-shifter.kicad_sch
kicad-cli sch export netlist --format kicadsexpr -o net.txt nri-g13-shifter.kicad_sch
python3 gen_pcb.py                                    # плата
kicad-cli pcb drc --refill-zones --save-board --schematic-parity nri-g13-shifter.kicad_pcb
```

`gen_pcb.py` берёт цепи, номиналы и посадочные места **из нетлиста схемы**, а
не задаёт их заново: разойтись со схемой они не могут в принципе.

`--refill-zones --save-board` обязателен: скрипт описывает контур заливки, а
заполняет её KiCad. Без этого шага плата откроется с пустыми зонами.

Определения символов скрипт берёт из установленных библиотек KiCad и встраивает
в файл целиком: распиновка BSS138 и разъёмов настоящая, а схема при этом
открывается на машине без этих библиотек.

## Состояние

Проверено средствами KiCad 10:

| Проверка | Результат |
|---|---|
| ERC схемы | 0 нарушений |
| DRC платы | 0 нарушений |
| Неразведённые связи | 0 |
| Сверка платы со схемой | 0 расхождений |

Нетлист вдобавок сверен с замыслом по каждому контакту вручную.

**Плата не изготавливалась и не собиралась.** Всё сказанное — про файлы,
а не про железо.

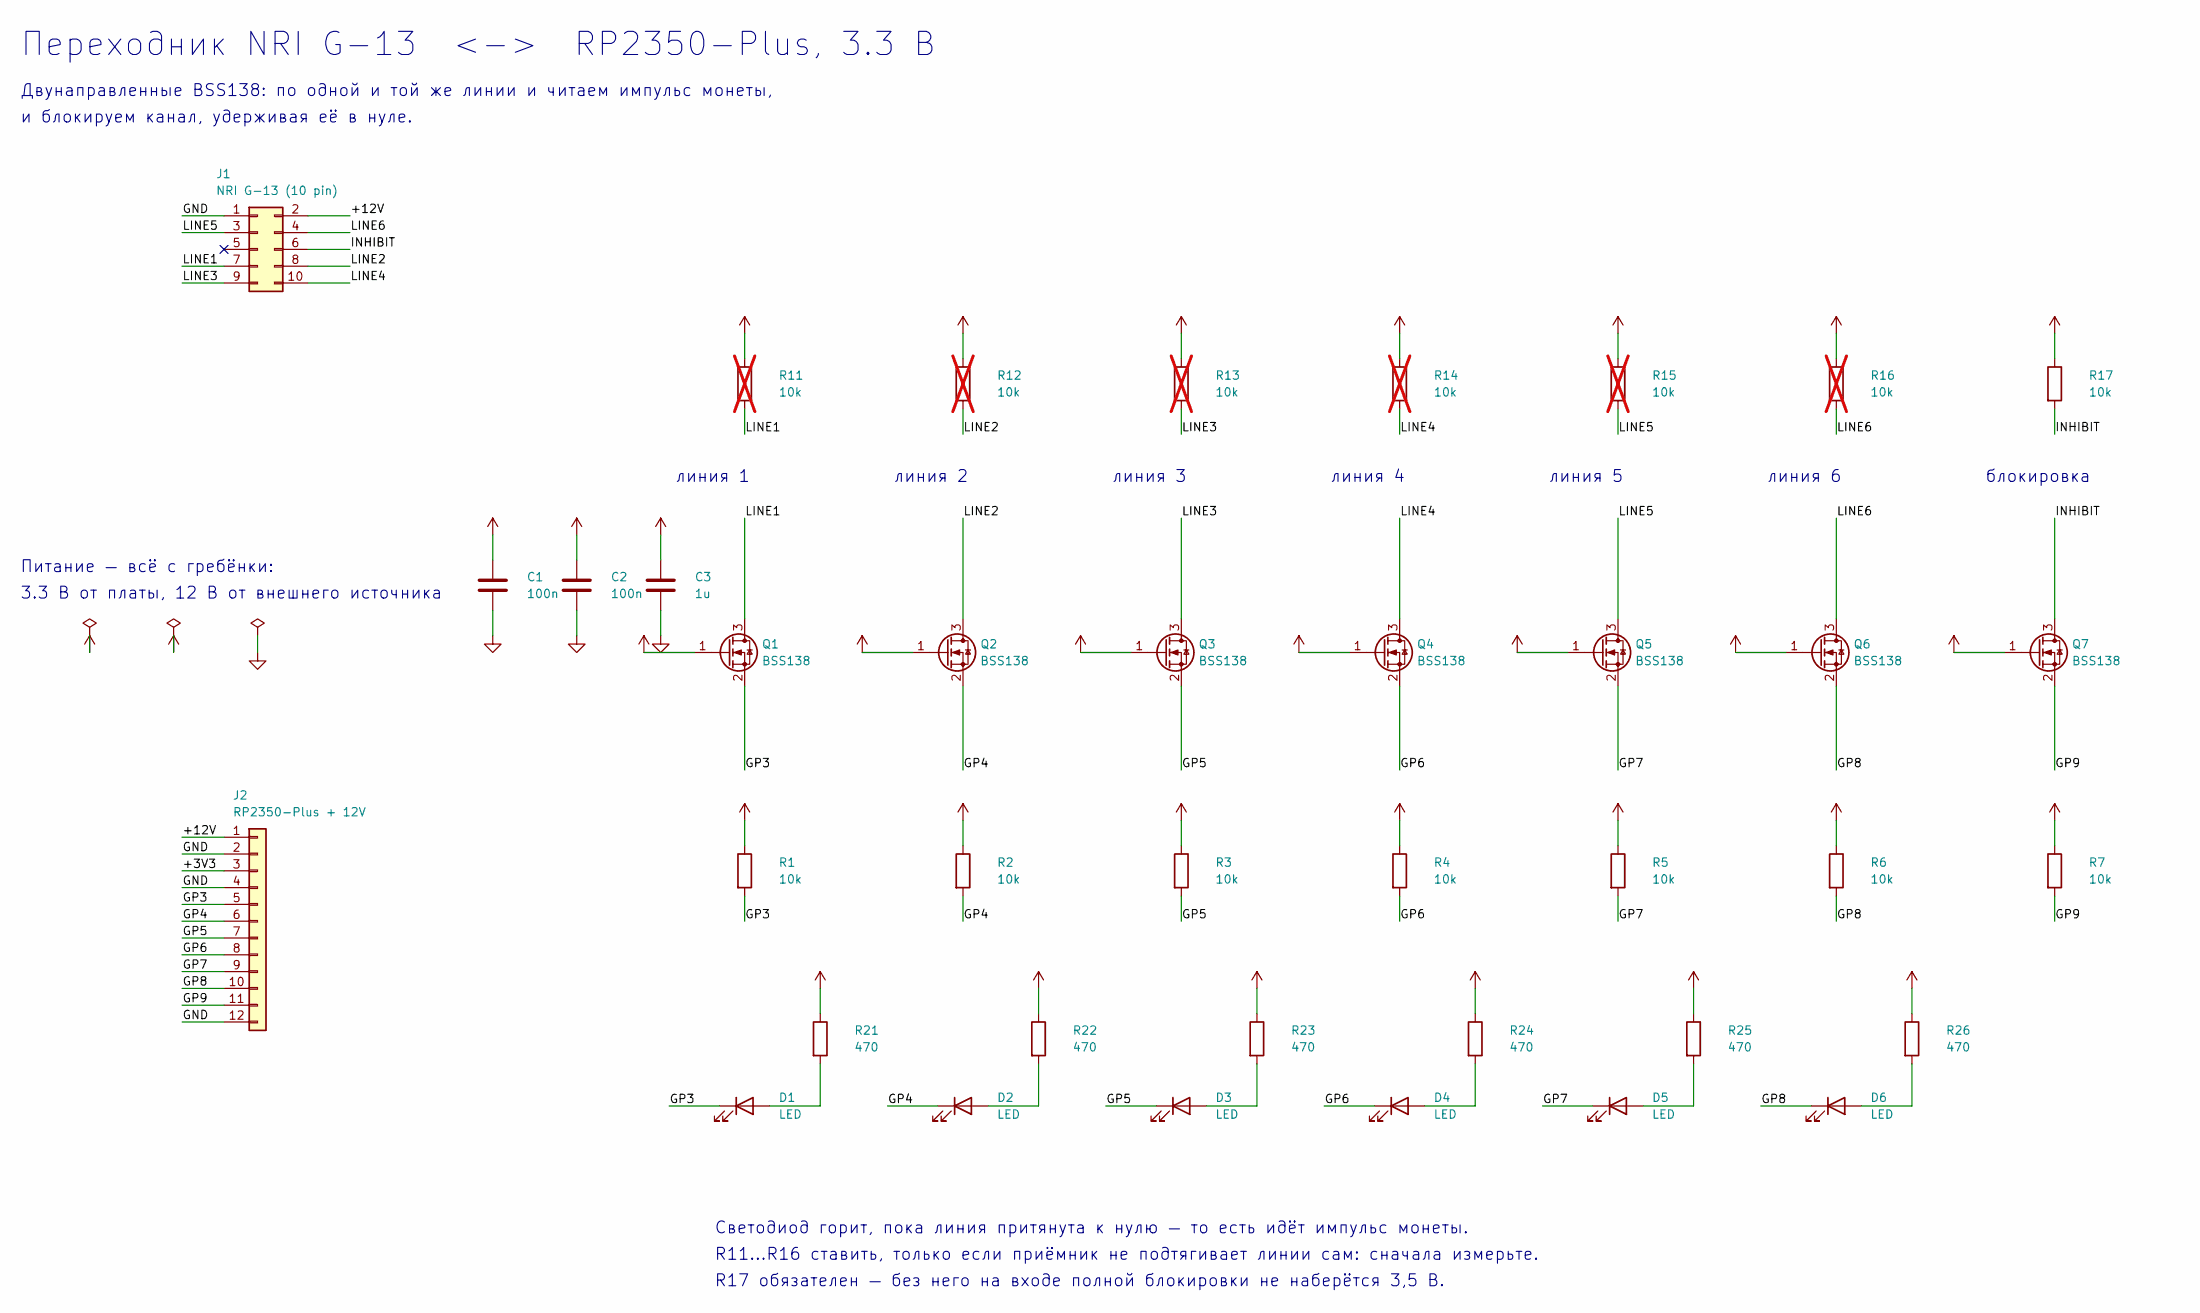
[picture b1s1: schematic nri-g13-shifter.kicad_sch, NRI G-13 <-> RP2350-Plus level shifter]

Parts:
C1, C2: 100n; C_0603_1608Metric; LCSC C14663
C3: 1u; C_0603_1608Metric; LCSC C15849
D1, D2, D3, D4, D5, D6: LED; LED_0603_1608Metric; LCSC C2286
J1: NRI G-13 (10 pin); IDC-Header_2x05_P2.54mm_Vertical
J2: RP2350-Plus + 12V; PinHeader_1x12_P2.54mm_Vertical
Q1, Q2, Q3, Q4, Q5, Q6, Q7: BSS138; SOT-23; LCSC C78284
R1, R2, R3, R4, R5, R6, R7, R17: 10k; R_0603_1608Metric; LCSC C25804
R11, R12, R13, R14, R15, R16: 10k; R_0603_1608Metric; LCSC C25804; not fitted
R21, R22, R23, R24, R25, R26: 470; R_0603_1608Metric; LCSC C23179

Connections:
+3V3: C1.1, J2.3, Q1.1 (G), Q2.1 (G), Q3.1 (G), Q4.1 (G), Q5.1 (G), Q6.1 (G), Q7.1 (G), R1.1, R2.1, R3.1, R4.1, R5.1, R6.1, R7.1, R21.1, R22.1, R23.1, R24.1, R25.1, R26.1
+12V: C2.1, C3.1, J1.2, J2.1, R11.1, R12.1, R13.1, R14.1, R15.1, R16.1, R17.1
/GP3: D1.1 (K), J2.5, Q1.2 (S), R1.2
/GP4: D2.1 (K), J2.6, Q2.2 (S), R2.2
/GP5: D3.1 (K), J2.7, Q3.2 (S), R3.2
/GP6: D4.1 (K), J2.8, Q4.2 (S), R4.2
/GP7: D5.1 (K), J2.9, Q5.2 (S), R5.2
/GP8: D6.1 (K), J2.10, Q6.2 (S), R6.2
/GP9: J2.11, Q7.2 (S), R7.2
/INHIBIT: J1.6, Q7.3 (D), R17.2
/LINE1: J1.7, Q1.3 (D), R11.2
/LINE2: J1.8, Q2.3 (D), R12.2
/LINE3: J1.9, Q3.3 (D), R13.2
/LINE4: J1.10, Q4.3 (D), R14.2
/LINE5: J1.3, Q5.3 (D), R15.2
/LINE6: J1.4, Q6.3 (D), R16.2
GND: C1.2, C2.2, C3.2, J1.1, J2.2, J2.4, J2.12
unnamed: D1.2 (A), R21.2
unnamed: D2.2 (A), R22.2
unnamed: D3.2 (A), R23.2
unnamed: D4.2 (A), R24.2
unnamed: D5.2 (A), R25.2
unnamed: D6.2 (A), R26.2

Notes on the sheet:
Переходник NRI G-13 <-> RP2350-Plus, 3.3 В
Двунаправленные BSS138: по одной и той же линии и читаем импульс монеты,
и блокируем канал, удерживая её в нуле.
Питание — всё с гребёнки:
3.3 В от платы, 12 В от внешнего источника
линия 1
линия 2
линия 3
линия 4
линия 5
линия 6
блокировка
Светодиод горит, пока линия притянута к нулю — то есть идёт импульс монеты.
R11…R16 ставить, только если приёмник не подтягивает линии сам: сначала измерьте.
R17 обязателен — без него на входе полной блокировки не наберётся 3,5 В.

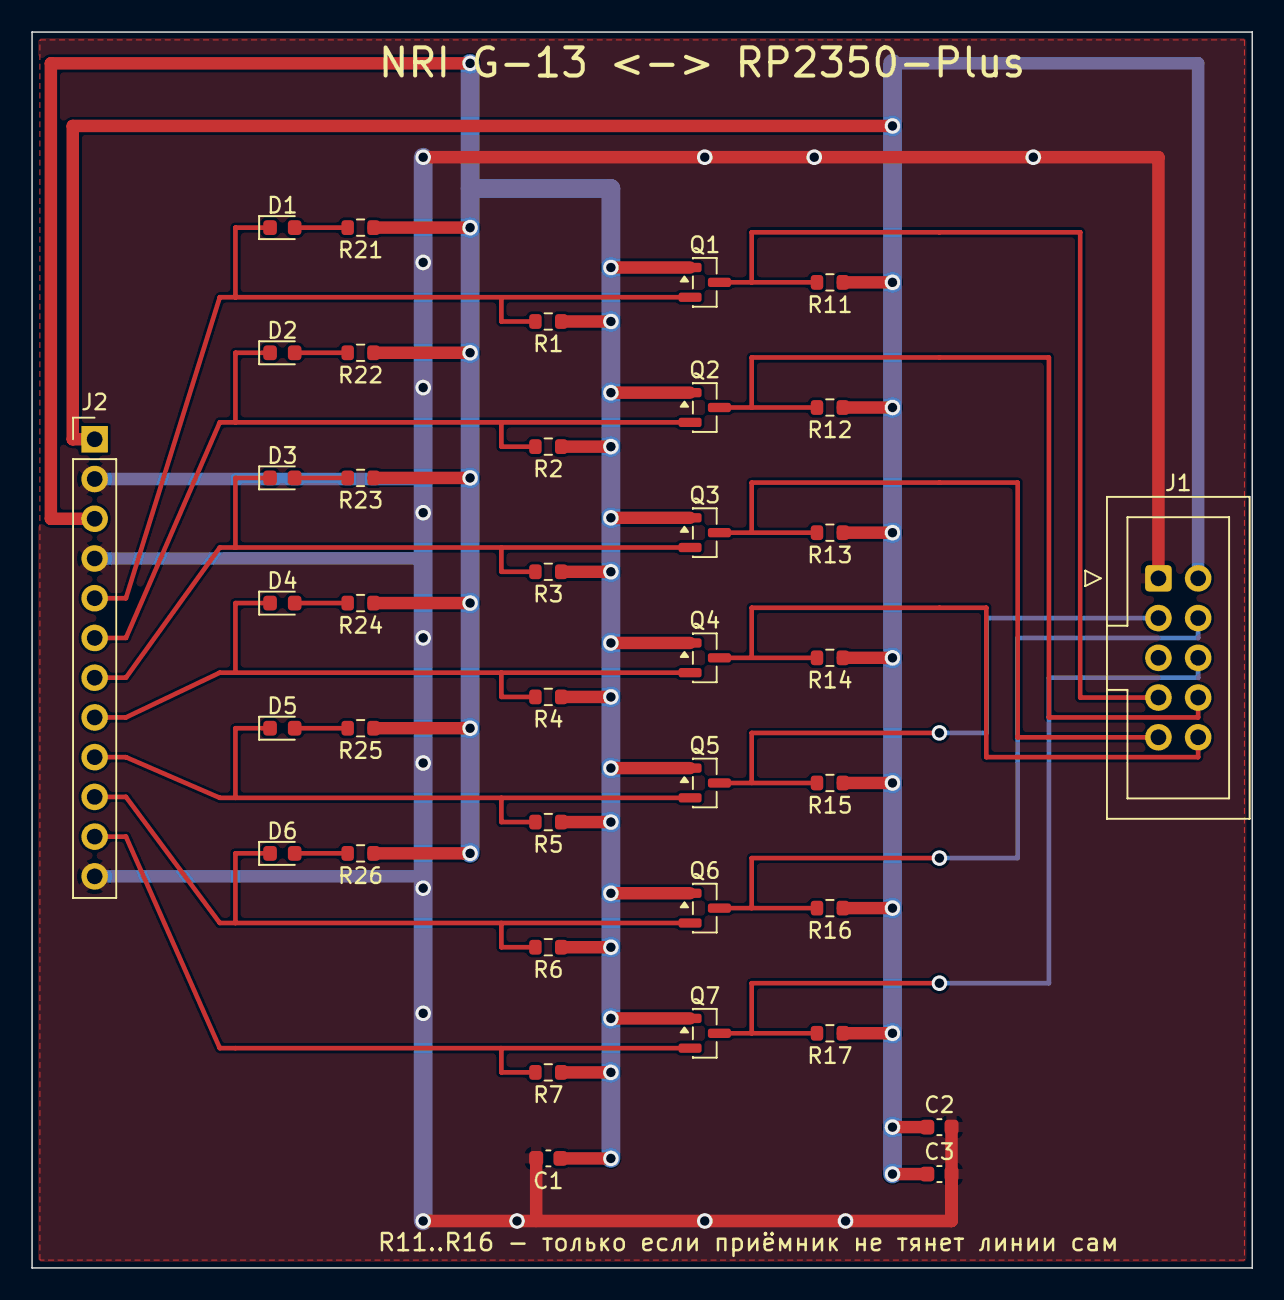
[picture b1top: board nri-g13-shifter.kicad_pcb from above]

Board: 2 copper layers, 78.0 x 79.0 mm, 38 parts (0 on the bottom side), 23 nets.

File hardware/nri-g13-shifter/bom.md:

# Спецификация

| Позиция | Номинал | Корпус | Ставить |
|---|---|---|---|
| C1 | 100n | C_0603_1608Metric | да |
| C2 | 100n | C_0603_1608Metric | да |
| C3 | 1u | C_0603_1608Metric | да |
| D1 | LED | LED_0603_1608Metric | да |
| D2 | LED | LED_0603_1608Metric | да |
| D3 | LED | LED_0603_1608Metric | да |
| D4 | LED | LED_0603_1608Metric | да |
| D5 | LED | LED_0603_1608Metric | да |
| D6 | LED | LED_0603_1608Metric | да |
| J1 | NRI G-13 (10 pin) | IDC-Header_2x05_P2.54mm_Vertical | да |
| J2 | RP2350-Plus + 12V | PinHeader_1x12_P2.54mm_Vertical | да |
| Q1 | BSS138 | SOT-23 | да |
| Q2 | BSS138 | SOT-23 | да |
| Q3 | BSS138 | SOT-23 | да |
| Q4 | BSS138 | SOT-23 | да |
| Q5 | BSS138 | SOT-23 | да |
| Q6 | BSS138 | SOT-23 | да |
| Q7 | BSS138 | SOT-23 | да |
| R1 | 10k | R_0603_1608Metric | да |
| R2 | 10k | R_0603_1608Metric | да |
| R3 | 10k | R_0603_1608Metric | да |
| R4 | 10k | R_0603_1608Metric | да |
| R5 | 10k | R_0603_1608Metric | да |
| R6 | 10k | R_0603_1608Metric | да |
| R7 | 10k | R_0603_1608Metric | да |
| R11 | 10k | R_0603_1608Metric | нет (по месту) |
| R12 | 10k | R_0603_1608Metric | нет (по месту) |
| R13 | 10k | R_0603_1608Metric | нет (по месту) |
| R14 | 10k | R_0603_1608Metric | нет (по месту) |
| R15 | 10k | R_0603_1608Metric | нет (по месту) |
| R16 | 10k | R_0603_1608Metric | нет (по месту) |
| R17 | 10k | R_0603_1608Metric | да |
| R21 | 470 | R_0603_1608Metric | да |
| R22 | 470 | R_0603_1608Metric | да |
| R23 | 470 | R_0603_1608Metric | да |
| R24 | 470 | R_0603_1608Metric | да |
| R25 | 470 | R_0603_1608Metric | да |
| R26 | 470 | R_0603_1608Metric | да |
